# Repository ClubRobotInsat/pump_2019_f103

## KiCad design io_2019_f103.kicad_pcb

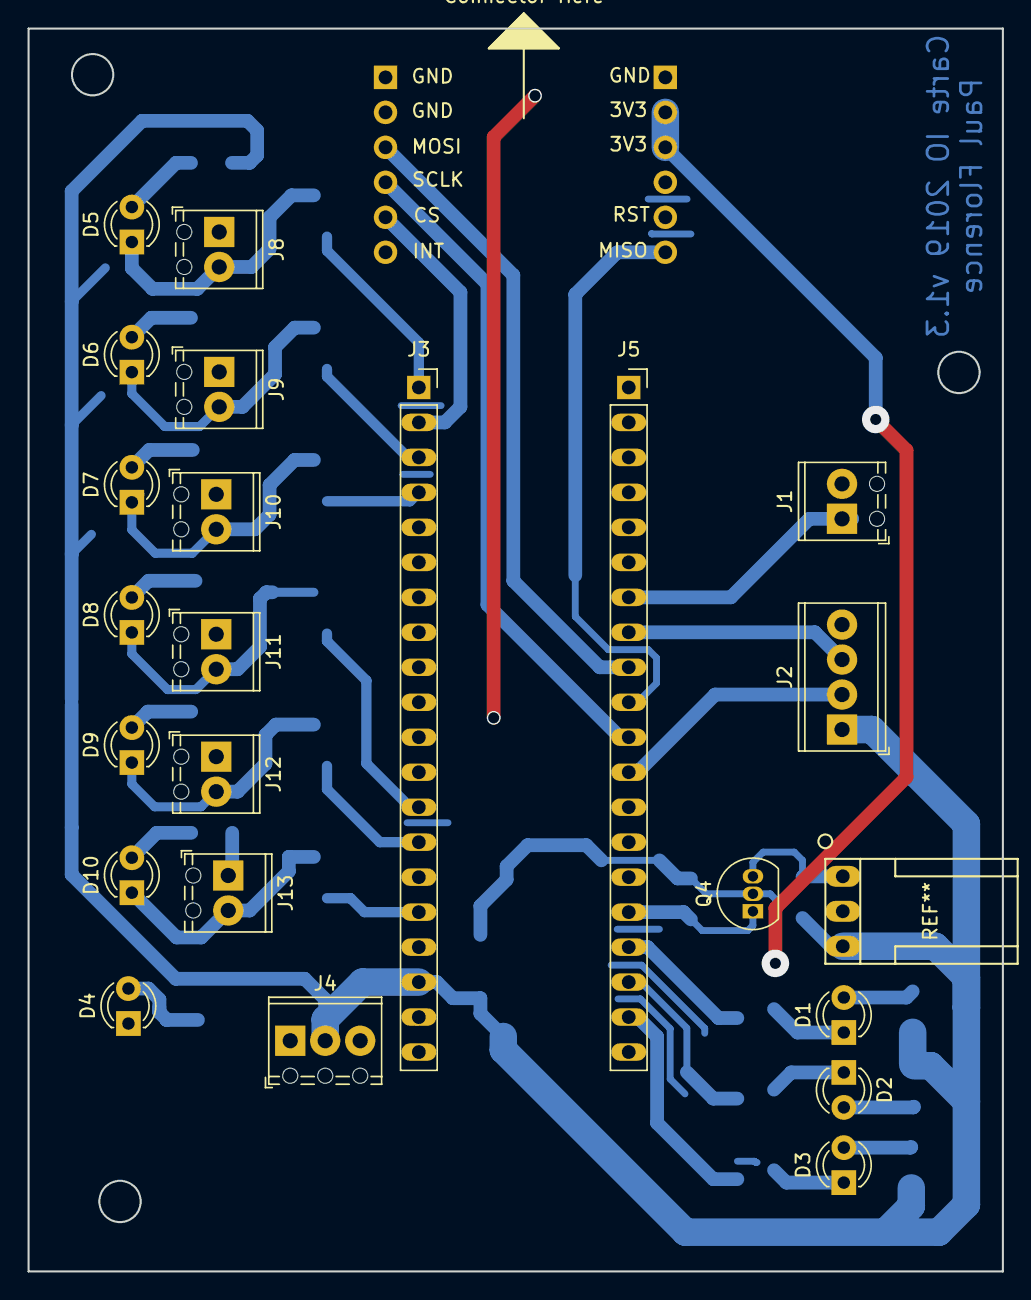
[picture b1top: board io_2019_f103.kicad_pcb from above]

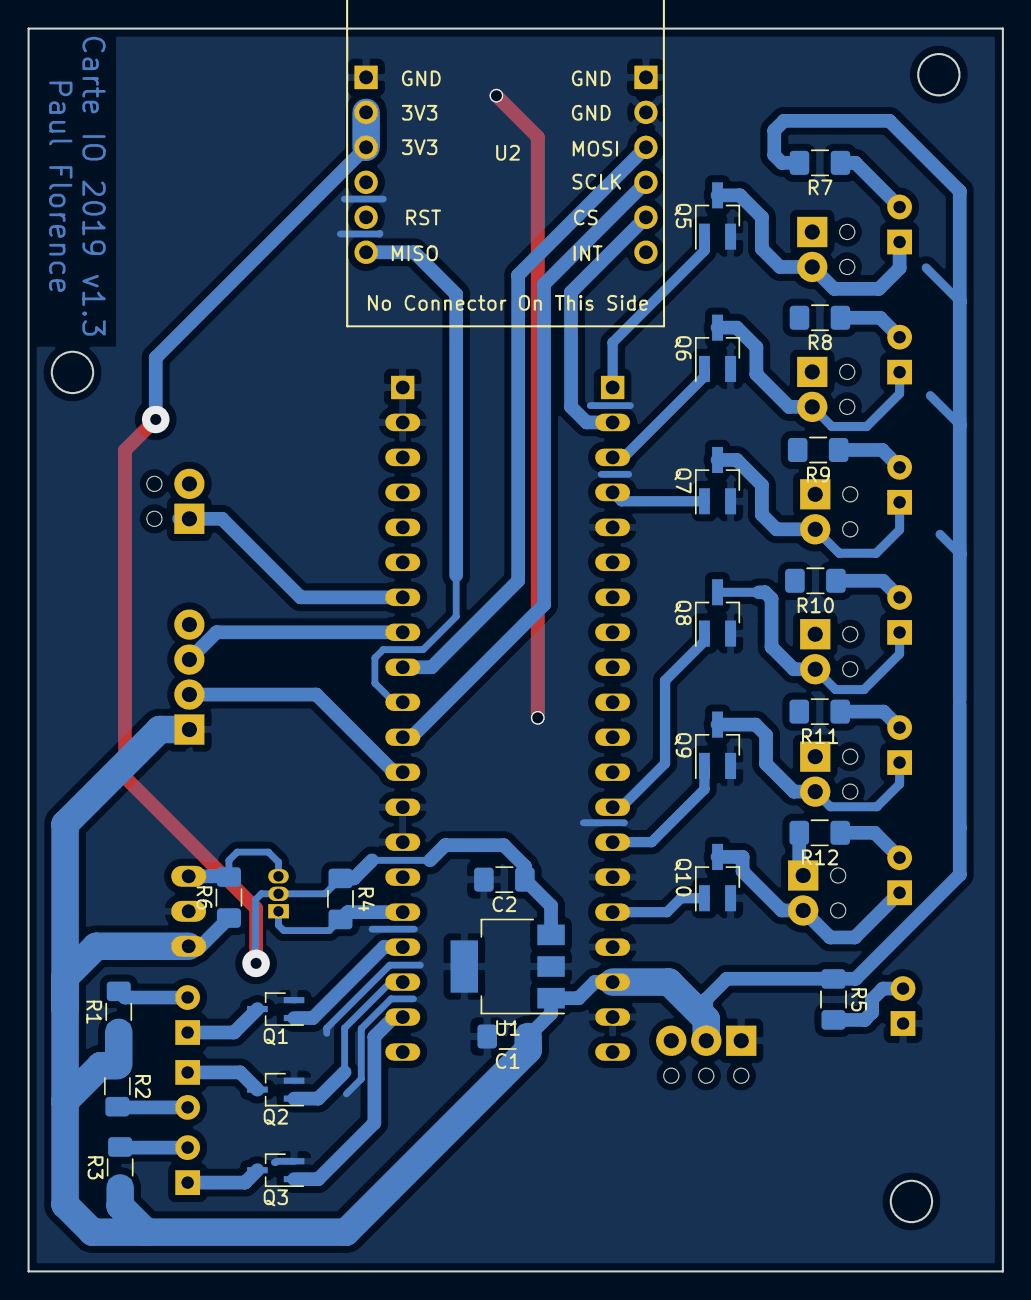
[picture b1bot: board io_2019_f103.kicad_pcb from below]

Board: 2 copper layers, 70.8 x 90.2 mm, 48 parts (24 on the bottom side), 40 nets.

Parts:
C1, C2: 1u; C_1206_3216Metric_Pad1.42x1.75mm_HandSolder
D1: LED_hardfault_jaune; LED_D3.0mm
D2: LED_communication_vert; LED_D3.0mm
D3: led_feedback_vert; LED_D3.0mm
D4: LED_alimentation_rouge; LED_D3.0mm
D5, D6, D7, D8, D9, D10: LED_VERTE; LED_D3.0mm
J1: Con_Tirette; TerminalBlock_Phoenix_MPT-0,5-2-2.54_1x02_P2.54mm_Horizontal
J2: Conn_01x04; TerminalBlock_Phoenix_MPT-0,5-4-2.54_1x04_P2.54mm_Horizontal
J3, J5: Conn_01x20_Female; PinSocket_1x20_P2.54mm_Vertical_Long_Pads
J4: Alim logique; TerminalBlock_Phoenix_MPT-0,5-3-2.54_1x03_P2.54mm_Horizontal
J7: Con_Buzzer; HE14-3_horizontal
J8, J9, J10, J11, J12, J13: Con_EV; TerminalBlock_Phoenix_MPT-0,5-2-2.54_1x02_P2.54mm_Horizontal
Q1, Q2, Q3: PMF370XN; SOT-323_SC-70_Handsoldering
Q4: 2N7000; TO-92_Inline
Q5, Q6, Q7, Q8, Q9, Q10: NDS351AN; SOT-23_Handsoldering
R1, R2, R3, R5: 150; R_1206_3216Metric_Pad1.42x1.75mm_HandSolder
R4, R6: 10k; R_1206_3216Metric_Pad1.42x1.75mm_HandSolder
R7, R8, R9, R10, R11, R12: 150R; R_1206_3216Metric_Pad1.42x1.75mm_HandSolder
U1: TC1262-33; SOT-223-3_TabPin2
U2: w5500

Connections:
+3V3: C2.1, J1.1, Q4.2, R4.1, U1.3, U2.10, U2.11
+5V: C1.1, J2.2, J3.18, J4.2, J7.3, J8.1, J9.1, J10.1, J11.1, J12.1, J13.1, R1.1, R2.1, R3.1, R5.1, R6.1, R7.2, R8.2, R9.2, R10.2, R11.2, R12.2, U1.1
/Buzzer: J5.16, Q4.1, R4.2
/CS: J3.2, U2.2
/EV1: J3.1, Q5.1
/EV2: J3.3, Q6.1
/EV3: J3.4, Q7.1
/EV4: J3.13, Q8.1
/EV5: J3.14, Q9.1
/EV6: J3.16, Q10.1
/MISO: J5.10, U2.7
/MOSI: J5.9, U2.4
/Pompe1: J2.3, J5.12
/Pompe2: J2.4, J5.8
/SCK: J5.11, U2.3
/Tirette: J1.2, J5.7
/led_communication: J5.18, Q2.1
/led_feedback: J5.19, Q3.1
/led_hardfault: J5.17, Q1.1
GND: C1.2, C2.2, D4.1, J2.1, J3.5, J3.15, J3.17, J3.19, J4.1, J5.1, J5.2, J5.13, J5.14, J7.2, Q1.2, Q2.2, Q3.2, Q5.2, Q6.2, Q7.2, Q8.2, Q9.2, Q10.2, U1.2, U2.5, U2.6, U2.12
unnamed: D1.1, Q1.3
unnamed: D1.2, R1.2
unnamed: D2.1, Q2.3
unnamed: D2.2, R2.2
unnamed: D3.1, Q3.3
unnamed: D3.2, R3.2
unnamed: D4.2, R5.2
unnamed: D5.1, J8.2, Q5.3
unnamed: D5.2, R7.1
unnamed: D6.1, J9.2, Q6.3
unnamed: D6.2, R8.1
unnamed: D7.1, J10.2, Q7.3
unnamed: D7.2, R9.1
unnamed: D8.1, J11.2, Q8.3
unnamed: D8.2, R10.1
unnamed: D9.1, J12.2, Q9.3
unnamed: D9.2, R11.1
unnamed: D10.1, J13.2, Q10.3
unnamed: D10.2, R12.1
unnamed: J7.1, Q4.3, R6.2

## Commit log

2018-11-25 First design.
2018-12-20 Ajout connecteurs blackpill
2019-03-21 Ajout resistances transistor
2019-04-04 No optocoupleur
2019-05-09 Nouvelle carte pump
2019-05-09 Les MOS manquent
2019-05-11 First version
2019-05-11 Add drill hole, and version text
2019-05-11 Fix reference for mofset (NDS351AN)
2019-05-11 Modification driver electrovannes
2019-05-11 Bump version number
2019-05-11 Fix the mosfet drivers (sch only)
2019-05-11 fix the pcb
2019-05-11 actually fix the ev driver
2019-05-11 Update pcb to take into account fixes made by @dotsumae
2019-05-13 Add a little bit of margin on the side of the PCB Scale up vias copper pad so that it will be easier to solder
2019-05-16 Update connector footprint
